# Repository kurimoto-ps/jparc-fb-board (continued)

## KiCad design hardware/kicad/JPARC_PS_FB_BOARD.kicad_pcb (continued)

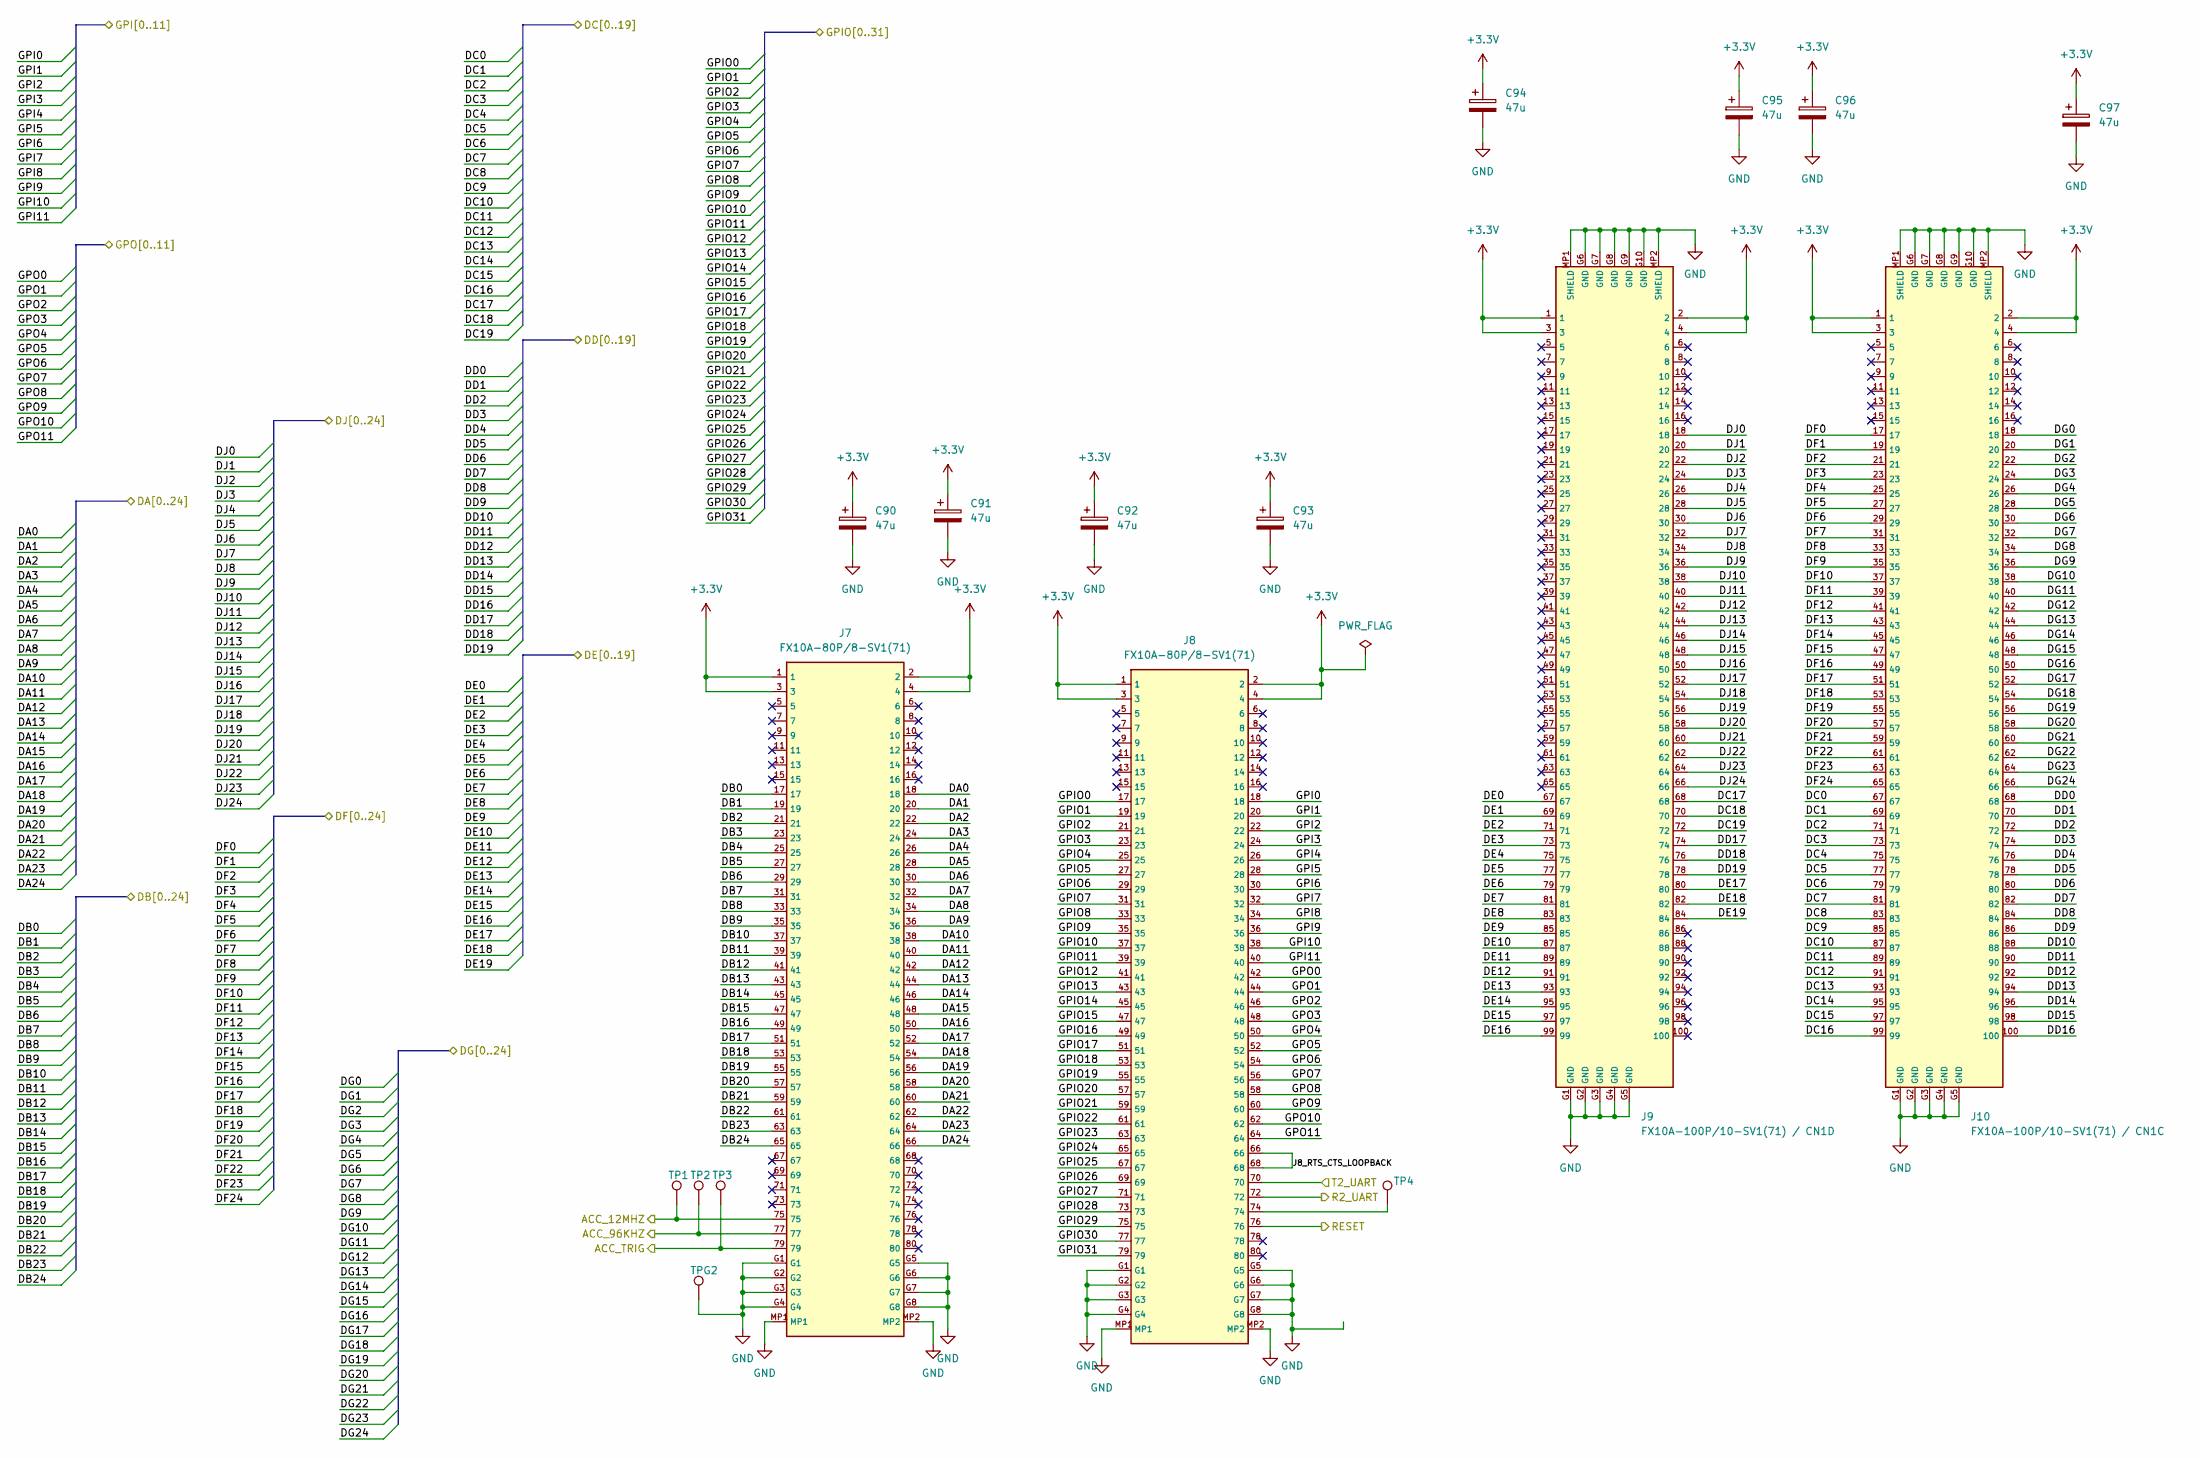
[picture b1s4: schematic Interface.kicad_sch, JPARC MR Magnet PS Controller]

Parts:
C90, C91, C92, C93, C94, C95, C96, C97: 47u; CP_Elec_5x5.8
J7, J8: FX10A-80P/8-SV1(71); Hirose_FX10A_80P_8_SV1_BossHoles
J9: FX10A-100P/10-SV1(71) / CN1D; Hirose_FX10A_100P_10_SV1_BossHoles
J10: FX10A-100P/10-SV1(71) / CN1C; Hirose_FX10A_100P_10_SV1_BossHoles
TP1, TP2, TP3, TP4: TestPoint_THTPad_D1.0mm_Drill0.5mm
TPG2: TestPoint_THTPad_D1.0mm_Drill0.5mm

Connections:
+3.3V: C90.1, C91.1, C92.1, C93.1, C94.1, C95.1, C96.1, C97.1, J7.1, J7.2, J7.3, J7.4, J8.1, J8.2, J8.3, J8.4, J9.1, J9.2, J9.3, J9.4, J10.1, J10.2, J10.3, J10.4; also elsewhere on the board
/Interface Sheet/ACC_12MHZ: J7.75, TP1.1 (1_1); also elsewhere on the board
/Interface Sheet/ACC_TRIG: J7.79, TP3.1 (1_1); also elsewhere on the board
/Interface Sheet/DA0: J7.18; also elsewhere on the board
/Interface Sheet/DA1: J7.20; also elsewhere on the board
/Interface Sheet/DA2: J7.22; also elsewhere on the board
/Interface Sheet/DA3: J7.24; also elsewhere on the board
/Interface Sheet/DA4: J7.26; also elsewhere on the board
/Interface Sheet/DA5: J7.28; also elsewhere on the board
/Interface Sheet/DA6: J7.30; also elsewhere on the board
/Interface Sheet/DA7: J7.32; also elsewhere on the board
/Interface Sheet/DA8: J7.34; also elsewhere on the board
/Interface Sheet/DA9: J7.36; also elsewhere on the board
/Interface Sheet/DA10: J7.38; also elsewhere on the board
/Interface Sheet/DA11: J7.40; also elsewhere on the board
/Interface Sheet/DA12: J7.42; also elsewhere on the board
/Interface Sheet/DA13: J7.44; also elsewhere on the board
/Interface Sheet/DA14: J7.46; also elsewhere on the board
/Interface Sheet/DA15: J7.48; also elsewhere on the board
/Interface Sheet/DA16: J7.50; also elsewhere on the board
/Interface Sheet/DA17: J7.52; also elsewhere on the board
/Interface Sheet/DA18: J7.54; also elsewhere on the board
/Interface Sheet/DA19: J7.56; also elsewhere on the board
/Interface Sheet/DA20: J7.58; also elsewhere on the board
/Interface Sheet/DA21: J7.60; also elsewhere on the board
/Interface Sheet/DA22: J7.62; also elsewhere on the board
/Interface Sheet/DA23: J7.64; also elsewhere on the board
/Interface Sheet/DA24: J7.66; also elsewhere on the board
/Interface Sheet/DB0: J7.17; also elsewhere on the board
/Interface Sheet/DB1: J7.19; also elsewhere on the board
/Interface Sheet/DB2: J7.21; also elsewhere on the board
/Interface Sheet/DB3: J7.23; also elsewhere on the board
/Interface Sheet/DB4: J7.25; also elsewhere on the board
/Interface Sheet/DB5: J7.27; also elsewhere on the board
/Interface Sheet/DB6: J7.29; also elsewhere on the board
/Interface Sheet/DB7: J7.31; also elsewhere on the board
/Interface Sheet/DB8: J7.33; also elsewhere on the board
/Interface Sheet/DB9: J7.35; also elsewhere on the board
/Interface Sheet/DB10: J7.37; also elsewhere on the board
/Interface Sheet/DB11: J7.39; also elsewhere on the board
/Interface Sheet/DB12: J7.41; also elsewhere on the board
/Interface Sheet/DB13: J7.43; also elsewhere on the board
/Interface Sheet/DB14: J7.45; also elsewhere on the board
/Interface Sheet/DB15: J7.47; also elsewhere on the board
/Interface Sheet/DB16: J7.49; also elsewhere on the board
/Interface Sheet/DB17: J7.51; also elsewhere on the board
/Interface Sheet/DB18: J7.53; also elsewhere on the board
/Interface Sheet/DB19: J7.55; also elsewhere on the board
/Interface Sheet/DB20: J7.57; also elsewhere on the board
/Interface Sheet/DB21: J7.59; also elsewhere on the board
/Interface Sheet/DB22: J7.61; also elsewhere on the board
/Interface Sheet/DB23: J7.63; also elsewhere on the board
/Interface Sheet/DB24: J7.65; also elsewhere on the board
/Interface Sheet/DC0: J10.67; also elsewhere on the board
/Interface Sheet/DC1: J10.69; also elsewhere on the board
/Interface Sheet/DC2: J10.71; also elsewhere on the board
/Interface Sheet/DC3: J10.73; also elsewhere on the board
/Interface Sheet/DC4: J10.75; also elsewhere on the board
/Interface Sheet/DC5: J10.77; also elsewhere on the board
/Interface Sheet/DC6: J10.79; also elsewhere on the board
/Interface Sheet/DC7: J10.81; also elsewhere on the board
/Interface Sheet/DC8: J10.83; also elsewhere on the board
/Interface Sheet/DC9: J10.85; also elsewhere on the board
/Interface Sheet/DC10: J10.87; also elsewhere on the board
/Interface Sheet/DC11: J10.89; also elsewhere on the board
/Interface Sheet/DC12: J10.91; also elsewhere on the board
/Interface Sheet/DC13: J10.93; also elsewhere on the board
/Interface Sheet/DC14: J10.95; also elsewhere on the board
/Interface Sheet/DC15: J10.97; also elsewhere on the board
/Interface Sheet/DC16: J10.99; also elsewhere on the board
/Interface Sheet/DC17: J9.68; also elsewhere on the board
/Interface Sheet/DC18: J9.70; also elsewhere on the board
/Interface Sheet/DC19: J9.72; also elsewhere on the board
/Interface Sheet/DD0: J10.68; also elsewhere on the board
/Interface Sheet/DD1: J10.70; also elsewhere on the board
/Interface Sheet/DD2: J10.72; also elsewhere on the board
/Interface Sheet/DD3: J10.74; also elsewhere on the board
/Interface Sheet/DD4: J10.76; also elsewhere on the board
/Interface Sheet/DD5: J10.78; also elsewhere on the board
/Interface Sheet/DD6: J10.80; also elsewhere on the board
/Interface Sheet/DD7: J10.82; also elsewhere on the board
/Interface Sheet/DD8: J10.84; also elsewhere on the board
/Interface Sheet/DD9: J10.86; also elsewhere on the board
/Interface Sheet/DD10: J10.88; also elsewhere on the board
/Interface Sheet/DD11: J10.90; also elsewhere on the board
/Interface Sheet/DD12: J10.92; also elsewhere on the board
/Interface Sheet/DD13: J10.94; also elsewhere on the board
/Interface Sheet/DD14: J10.96; also elsewhere on the board
/Interface Sheet/DD15: J10.98; also elsewhere on the board
/Interface Sheet/DD16: J10.100; also elsewhere on the board
/Interface Sheet/DD17: J9.74; also elsewhere on the board
/Interface Sheet/DD18: J9.76; also elsewhere on the board
/Interface Sheet/DD19: J9.78; also elsewhere on the board
/Interface Sheet/DE0: J9.67; also elsewhere on the board
/Interface Sheet/DE1: J9.69; also elsewhere on the board
/Interface Sheet/DE2: J9.71; also elsewhere on the board
/Interface Sheet/DE3: J9.73; also elsewhere on the board
/Interface Sheet/DE4: J9.75; also elsewhere on the board
/Interface Sheet/DE5: J9.77; also elsewhere on the board
/Interface Sheet/DE6: J9.79; also elsewhere on the board
/Interface Sheet/DE7: J9.81; also elsewhere on the board
/Interface Sheet/DE8: J9.83; also elsewhere on the board
/Interface Sheet/DE9: J9.85; also elsewhere on the board
/Interface Sheet/DE10: J9.87; also elsewhere on the board
/Interface Sheet/DE11: J9.89; also elsewhere on the board
/Interface Sheet/DE12: J9.91; also elsewhere on the board
/Interface Sheet/DE13: J9.93; also elsewhere on the board
/Interface Sheet/DE14: J9.95; also elsewhere on the board
/Interface Sheet/DE15: J9.97; also elsewhere on the board
/Interface Sheet/DE16: J9.99; also elsewhere on the board
/Interface Sheet/DE17: J9.80; also elsewhere on the board
/Interface Sheet/DE18: J9.82; also elsewhere on the board
/Interface Sheet/DE19: J9.84; also elsewhere on the board
/Interface Sheet/DF0: J10.17; also elsewhere on the board
/Interface Sheet/DF1: J10.19; also elsewhere on the board
/Interface Sheet/DF2: J10.21; also elsewhere on the board
/Interface Sheet/DF3: J10.23; also elsewhere on the board
/Interface Sheet/DF4: J10.25; also elsewhere on the board
/Interface Sheet/DF5: J10.27; also elsewhere on the board
/Interface Sheet/DF6: J10.29; also elsewhere on the board
/Interface Sheet/DF7: J10.31; also elsewhere on the board
/Interface Sheet/DF8: J10.33; also elsewhere on the board
/Interface Sheet/DF9: J10.35; also elsewhere on the board
/Interface Sheet/DF10: J10.37; also elsewhere on the board
/Interface Sheet/DF11: J10.39; also elsewhere on the board
/Interface Sheet/DF12: J10.41; also elsewhere on the board
/Interface Sheet/DF13: J10.43; also elsewhere on the board
/Interface Sheet/DF14: J10.45; also elsewhere on the board
/Interface Sheet/DF15: J10.47; also elsewhere on the board
/Interface Sheet/DF16: J10.49; also elsewhere on the board
/Interface Sheet/DF17: J10.51; also elsewhere on the board
/Interface Sheet/DF18: J10.53; also elsewhere on the board
/Interface Sheet/DF19: J10.55; also elsewhere on the board
/Interface Sheet/DF20: J10.57; also elsewhere on the board
/Interface Sheet/DF21: J10.59; also elsewhere on the board
/Interface Sheet/DF22: J10.61; also elsewhere on the board
/Interface Sheet/DF23: J10.63; also elsewhere on the board
/Interface Sheet/DF24: J10.65; also elsewhere on the board
/Interface Sheet/DG0: J10.18; also elsewhere on the board
/Interface Sheet/DG1: J10.20; also elsewhere on the board
/Interface Sheet/DG2: J10.22; also elsewhere on the board
/Interface Sheet/DG3: J10.24; also elsewhere on the board
/Interface Sheet/DG4: J10.26; also elsewhere on the board
/Interface Sheet/DG5: J10.28; also elsewhere on the board
/Interface Sheet/DG6: J10.30; also elsewhere on the board
/Interface Sheet/DG7: J10.32; also elsewhere on the board
/Interface Sheet/DG8: J10.34; also elsewhere on the board
/Interface Sheet/DG9: J10.36; also elsewhere on the board
/Interface Sheet/DG10: J10.38; also elsewhere on the board
/Interface Sheet/DG11: J10.40; also elsewhere on the board
/Interface Sheet/DG12: J10.42; also elsewhere on the board
/Interface Sheet/DG13: J10.44; also elsewhere on the board
/Interface Sheet/DG14: J10.46; also elsewhere on the board
/Interface Sheet/DG15: J10.48; also elsewhere on the board
/Interface Sheet/DG16: J10.50; also elsewhere on the board
/Interface Sheet/DG17: J10.52; also elsewhere on the board
/Interface Sheet/DG18: J10.54; also elsewhere on the board
/Interface Sheet/DG19: J10.56; also elsewhere on the board
/Interface Sheet/DG20: J10.58; also elsewhere on the board
/Interface Sheet/DG21: J10.60; also elsewhere on the board
/Interface Sheet/DG22: J10.62; also elsewhere on the board
/Interface Sheet/DG23: J10.64; also elsewhere on the board
/Interface Sheet/DG24: J10.66; also elsewhere on the board
/Interface Sheet/DJ0: J9.18; also elsewhere on the board
/Interface Sheet/DJ1: J9.20; also elsewhere on the board
/Interface Sheet/DJ2: J9.22; also elsewhere on the board
/Interface Sheet/DJ3: J9.24; also elsewhere on the board
/Interface Sheet/DJ4: J9.26; also elsewhere on the board
/Interface Sheet/DJ5: J9.28; also elsewhere on the board
/Interface Sheet/DJ6: J9.30; also elsewhere on the board
/Interface Sheet/DJ7: J9.32; also elsewhere on the board
/Interface Sheet/DJ8: J9.34; also elsewhere on the board
/Interface Sheet/DJ9: J9.36; also elsewhere on the board
/Interface Sheet/DJ10: J9.38; also elsewhere on the board
/Interface Sheet/DJ11: J9.40; also elsewhere on the board
/Interface Sheet/DJ12: J9.42; also elsewhere on the board
/Interface Sheet/DJ13: J9.44; also elsewhere on the board
/Interface Sheet/DJ14: J9.46; also elsewhere on the board
/Interface Sheet/DJ15: J9.48; also elsewhere on the board
/Interface Sheet/DJ16: J9.50; also elsewhere on the board
/Interface Sheet/DJ17: J9.52; also elsewhere on the board
/Interface Sheet/DJ18: J9.54; also elsewhere on the board
/Interface Sheet/DJ19: J9.56; also elsewhere on the board
/Interface Sheet/DJ20: J9.58; also elsewhere on the board
/Interface Sheet/DJ21: J9.60; also elsewhere on the board
/Interface Sheet/DJ22: J9.62; also elsewhere on the board
/Interface Sheet/DJ23: J9.64; also elsewhere on the board
/Interface Sheet/DJ24: J9.66; also elsewhere on the board
/Interface Sheet/GPI0: J8.18; also elsewhere on the board
/Interface Sheet/GPI1: J8.20; also elsewhere on the board
/Interface Sheet/GPI2: J8.22; also elsewhere on the board
/Interface Sheet/GPI3: J8.24; also elsewhere on the board
/Interface Sheet/GPI4: J8.26; also elsewhere on the board
/Interface Sheet/GPI5: J8.28; also elsewhere on the board
/Interface Sheet/GPI6: J8.30; also elsewhere on the board
/Interface Sheet/GPI7: J8.32; also elsewhere on the board
/Interface Sheet/GPI8: J8.34; also elsewhere on the board
/Interface Sheet/GPI9: J8.36; also elsewhere on the board
/Interface Sheet/GPI10: J8.38; also elsewhere on the board
/Interface Sheet/GPI11: J8.40; also elsewhere on the board
/Interface Sheet/GPIO0: J8.17; also elsewhere on the board
/Interface Sheet/GPIO1: J8.19; also elsewhere on the board
/Interface Sheet/GPIO2: J8.21; also elsewhere on the board
/Interface Sheet/GPIO3: J8.23; also elsewhere on the board
/Interface Sheet/GPIO4: J8.25; also elsewhere on the board
/Interface Sheet/GPIO5: J8.27; also elsewhere on the board
/Interface Sheet/GPIO6: J8.29; also elsewhere on the board
/Interface Sheet/GPIO7: J8.31; also elsewhere on the board
/Interface Sheet/GPIO8: J8.33; also elsewhere on the board
/Interface Sheet/GPIO9: J8.35; also elsewhere on the board
/Interface Sheet/GPIO10: J8.37; also elsewhere on the board
/Interface Sheet/GPIO11: J8.39; also elsewhere on the board
/Interface Sheet/GPIO12: J8.41; also elsewhere on the board
/Interface Sheet/GPIO13: J8.43; also elsewhere on the board
/Interface Sheet/GPIO14: J8.45; also elsewhere on the board
/Interface Sheet/GPIO15: J8.47; also elsewhere on the board
/Interface Sheet/GPIO16: J8.49; also elsewhere on the board
/Interface Sheet/GPIO17: J8.51; also elsewhere on the board
/Interface Sheet/GPIO18: J8.53; also elsewhere on the board
/Interface Sheet/GPIO19: J8.55; also elsewhere on the board
/Interface Sheet/GPIO20: J8.57; also elsewhere on the board
/Interface Sheet/GPIO21: J8.59; also elsewhere on the board
/Interface Sheet/GPIO22: J8.61; also elsewhere on the board
/Interface Sheet/GPIO23: J8.63; also elsewhere on the board
/Interface Sheet/GPIO24: J8.65; also elsewhere on the board
/Interface Sheet/GPIO25: J8.67; also elsewhere on the board
/Interface Sheet/GPIO26: J8.69; also elsewhere on the board
/Interface Sheet/GPIO27: J8.71; also elsewhere on the board
/Interface Sheet/GPIO28: J8.73; also elsewhere on the board
/Interface Sheet/GPIO29: J8.75; also elsewhere on the board
/Interface Sheet/GPIO30: J8.77; also elsewhere on the board
/Interface Sheet/GPIO31: J8.79; also elsewhere on the board
/Interface Sheet/GPO0: J8.42; also elsewhere on the board
/Interface Sheet/GPO1: J8.44; also elsewhere on the board
/Interface Sheet/GPO2: J8.46; also elsewhere on the board
/Interface Sheet/GPO3: J8.48; also elsewhere on the board
/Interface Sheet/GPO4: J8.50; also elsewhere on the board
/Interface Sheet/GPO5: J8.52; also elsewhere on the board
/Interface Sheet/GPO6: J8.54; also elsewhere on the board
/Interface Sheet/GPO7: J8.56; also elsewhere on the board
/Interface Sheet/GPO8: J8.58; also elsewhere on the board
/Interface Sheet/GPO9: J8.60; also elsewhere on the board
/Interface Sheet/GPO10: J8.62; also elsewhere on the board
/Interface Sheet/GPO11: J8.64; also elsewhere on the board
/Interface Sheet/J8_RTS_CTS_LOOPBACK: J8.66, J8.68
/Interface Sheet/R2_UART: J8.72; also elsewhere on the board
/Interface Sheet/RESET: J8.76; also elsewhere on the board
/Interface Sheet/T2_UART: J8.70; also elsewhere on the board
/STM32H7 Sheet/PA0: J7.77, TP2.1 (1_1); also elsewhere on the board
GND: C90.2, C91.2, C92.2, C93.2, C94.2, C95.2, C96.2, C97.2, J7.G1, J7.G2, J7.G3, J7.G4, J7.G5, J7.G6, J7.G7, J7.G8, J7.MP1, J7.MP2, J8.G1, J8.G2, J8.G3, J8.G4, J8.G5, J8.G6, J8.G7, J8.G8, J8.MP1, J8.MP2, J9.G1 (GND), J9.G2 (GND), J9.G3 (GND), J9.G4 (GND), J9.G5 (GND), J9.G6 (GND), J9.G7 (GND), J9.G8 (GND), J9.G9 (GND), J9.G10 (GND), J9.MP1 (SHIELD), J9.MP2 (SHIELD), J10.G1 (GND), J10.G2 (GND), J10.G3 (GND), J10.G4 (GND), J10.G5 (GND), J10.G6 (GND), J10.G7 (GND), J10.G8 (GND), J10.G9 (GND), J10.G10 (GND), J10.MP1 (SHIELD), J10.MP2 (SHIELD), TPG2.1 (1_1); also elsewhere on the board
unnamed: J8.74, TP4.1 (1_1)
